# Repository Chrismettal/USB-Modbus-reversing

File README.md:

# USB-Modbus reversing <!-- omit in toc -->

Documentation of a reversed no-name USB to Modbus converter. It seems to be using some non-standard automatic `DE/NRE` handling that I would like to use for my [PiPLC project](https://github.com/chrismettal/piplc) for software that can't use manual `DE/NRE` switching, like Home Assistant.

A KiCAD project is included, but only for reversing the original PCB, and not to recreate a new one. Though I might change my mind later.

**If you like my work please consider [supporting me](https://github.com/Chrismettal#donations)!**

## Table of contents <!-- omit in toc -->

- [Original](#original)
- [Reversing](#reversing)
- [Observations](#observations)
- [Donations](#donations)
- [License](#license)

## Original

These cheap thingies are listed as RS485/Modbus CH340 based converters. The "`CH340`" in question is unlabeled on the board and does not seem to be a `CH340` at all.
Interestingly, some parts are not populated. The parts in question seem to be the Crystal for a real CH340 as well as a termination resistor on the Modbus line.

## Reversing

The board was completely depopulated, while the unlabeled parts were being measured. After cleaning the bare boards up, they were scanned with a regular flat bed scanner.

These scans were imported into KiCAD as layer images to trace over. All depopulated parts were created in the Schematic view and placed on the image. Routing without first creating the schematic doesn't work, so we hop back and forth, routing over the image and in the schematic at the same time, until all traces from the image are traced over and all parts are connected.

This let's us end up with the following schematic:

## Observations

- The part that I wanted to see, the automatic `DE/NRE` switching, seems to be super cheap and highly optimistic, switching on the sending driver while `DI` is being pulled `LOW`. This should mean that `A` only sends `LOW` signals actively, while relying on pullups to set `A` back `HIGH`.
- While being so cheap that it doesn't even use active `DE/NRE` switching, the device still has input protection on the `A/B` Modbus lines.
- It also doesn't have the option for a terminating resistor. You could place `R7` manually, but a switch on the side would have been nice.
- The "`CH340`" as described on Amazon is almost certainly not a `CH340`.
- The unpopulated Crystal has lines going to Vias that just don't go anywhere. It looks like the board was originally designed for an actual `CH340` with a crystal, but was quietly modified to accept a different USB converter. Seeing that the crystal's traces just end on a via I assume that they just didn't bother cleaning the rest of the board up when the converter IC was changed.

## Donations

**If you like my work please consider [supporting me](https://github.com/Chrismettal#donations)!**

## License

 <br />This work is licensed under a <a rel="license" href="http://creativecommons.org/licenses/by-sa/4.0/">Creative Commons Attribution-ShareAlike 4.0 International License</a>.

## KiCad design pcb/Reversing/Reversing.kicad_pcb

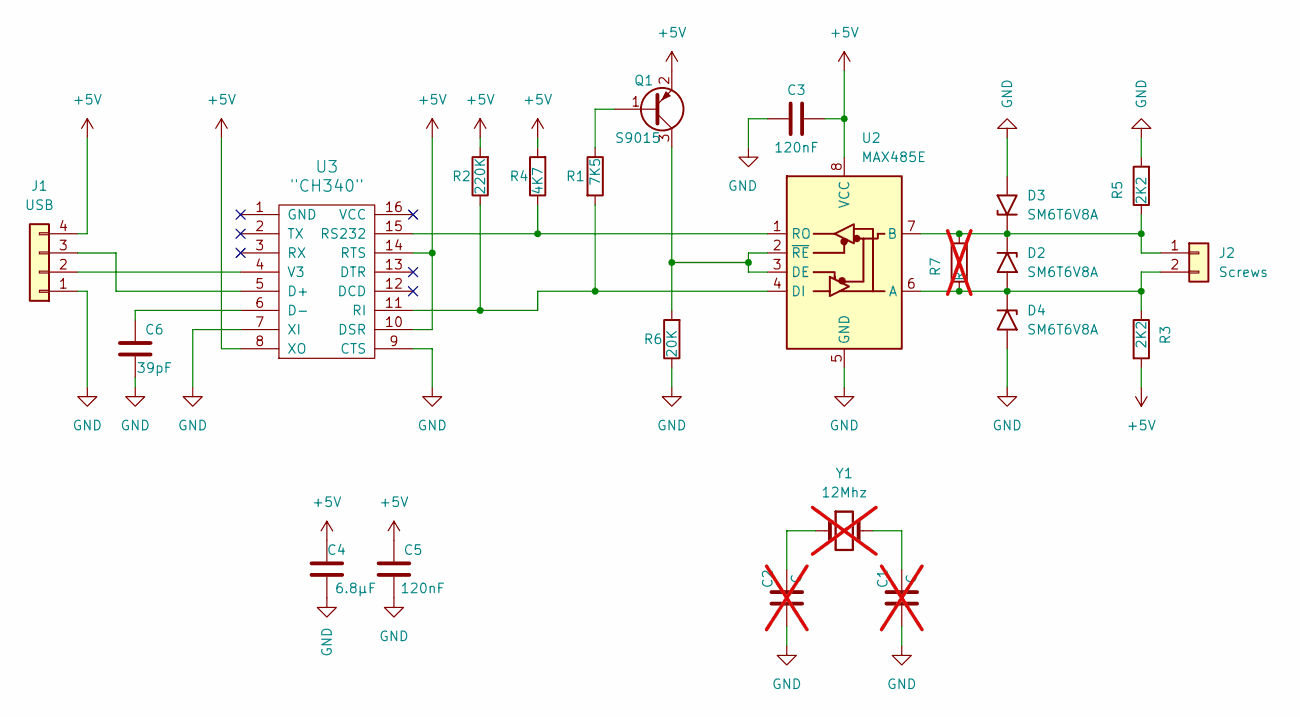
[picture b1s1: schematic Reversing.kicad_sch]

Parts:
C1, C2: C; C_0603_1608Metric; not fitted
C3, C5: 120nF; C_0603_1608Metric
C4: 6.8µF; C_0805_2012Metric
C6: 39pF; C_0603_1608Metric
D2, D3, D4: SM6T6V8A; D_SOD-123
J1: USB; PinHeader_1x04_P2.54mm_Vertical
J2: Screws; PinHeader_1x02_P2.54mm_Vertical
Q1: S9015; SOT-23; LCSC C2149
R1: 7K5; R_0603_1608Metric
R2: 220K; R_0603_1608Metric
R3, R5: 2K2; R_0603_1608Metric
R4: 4K7; R_0603_1608Metric
R6: 20K; R_0603_1608Metric
R7: R; R_0603_1608Metric; not fitted
U2: MAX485E; SO-8_3.9x4.9mm_P1.27mm
U3: "CH340"; SOIC-16_3.9x9.9mm_P1.27mm
Y1: 12Mhz; Crystal_HC18-U_Vertical; not fitted

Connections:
+5V: C3.1, C4.1, C5.2, J1.4, Q1.2 (E), R2.2, R3.2, R4.2, U2.8 (VCC), U3.8 (XO), U3.10 (DSR), U3.14 (RTS)
GND: C1.1, C2.1, C3.2, C4.2, C5.1, C6.2, D3.2 (A2), D4.2 (A2), J1.1, R5.2, R6.1, U2.5 (GND), U3.7 (XI), U3.9 (CTS)
unnamed: C1.2, Y1.2
unnamed: C2.2, Y1.1
unnamed: D2.1 (A1), D3.1 (A1), J2.1, R5.1, R7.2, U2.7 (B)
unnamed: D2.2 (A2), D4.1 (A1), J2.2, R3.1, R7.1, U2.6 (A)
unnamed: J1.2, U3.4 (V3)
unnamed: J1.3, U3.5 (D+)
unnamed: Q1.1 (B), R1.1
unnamed: Q1.3 (C), R6.2, U2.2 (~RE), U2.3 (DE)
unnamed: R1.2, R2.1, U2.4 (DI), U3.11 (RI)
unnamed: R4.1, U2.1 (RO), U3.15 (RS232)
unnamed: C6.1, U3.6 (D-)

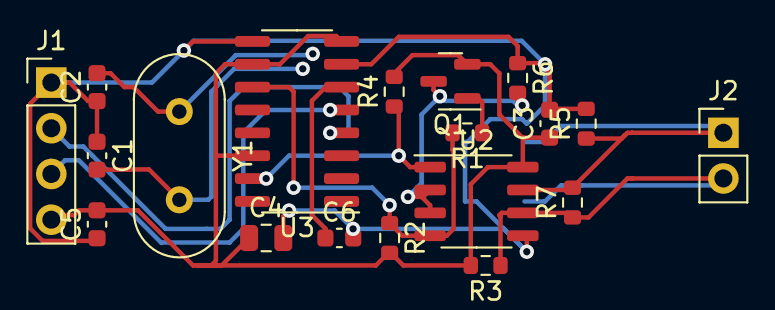
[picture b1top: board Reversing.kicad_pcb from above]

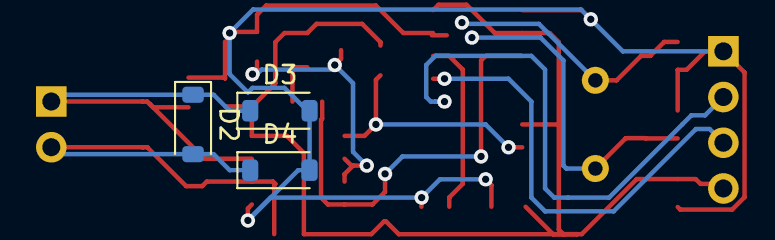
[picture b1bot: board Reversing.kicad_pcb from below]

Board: 2 copper layers, 22 parts (3 on the bottom side), 13 nets.

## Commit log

2024-01-21 Add initial project information
2024-01-21 Add assumed parts to KiCAD project
2024-01-21 Reverse whole board in one swoop
2024-01-21 Document observations
2024-01-21 Fix typo
2024-01-21 Fix Schematic embed

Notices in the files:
README.md:
License: CC BY-SA 4.0
